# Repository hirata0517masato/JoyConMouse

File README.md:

# JoyConMouse
ホームポジションを崩さずにマウス操作をしたかったので自作  

# 仕様（サンプルコード）
ジョイスティック：マウス操作  
右キー：左クリック  
中央キー：右クリック  
左キー＋ジョイスティック：スクロール  
左キー＋中央キー：進む  
左キー＋右キー：戻る  
中央キー＋ジョイスティック：マウス操作（速度UP）

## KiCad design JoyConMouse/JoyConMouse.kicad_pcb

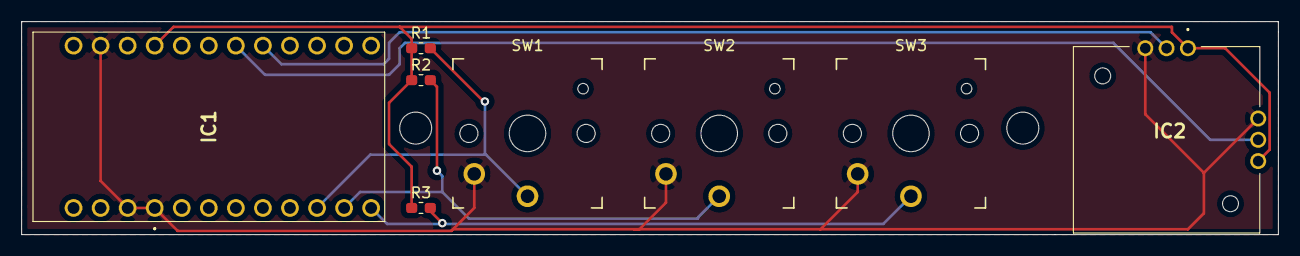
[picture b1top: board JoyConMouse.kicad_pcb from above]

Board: 2 copper layers, 118.0 x 20.0 mm, 8 parts (0 on the bottom side), 7 nets.

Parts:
IC1: DEV-12640; DEV12640
IC2: JT8P-3.2T-B10K-1-16Y; JT8P32TB10K116Y
R1, R2, R3: R; C_0603_1608Metric_Pad1.05x0.95mm_HandSolder
SW1, SW2, SW3: SW_Push; SW_PG1350

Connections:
+5V: IC1.18, IC2.A1, IC2.B1, R1.1, R2.1, R3.1
A0: IC1.A1, IC2.A2
A1: IC1.A2, IC2.B2
D7: IC1.7, R1.2, SW1.1
D8: IC1.8, R2.2, SW2.1
D9: IC1.9, R3.2, SW3.1
GND: IC1.1, IC1.20, IC1.24, IC2.A3, IC2.B3, SW1.2, SW2.2, SW3.2

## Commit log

2022-09-18 KiCad_date
    基板データの初回コミット
2022-09-25 first edition
    サンプルコードの作成および動作確認完了
2022-09-25 add_3D_body
    ケース用の３Dデータを追加
2022-09-25 Soft_Update
    コードの更新
    ・感度調整
    ・中央ボタンおしながらジョイスティック操作で通常時よりもはやくマウス操作ができる
2022-10-10 debug
    修正前：マウスの操作量が０の時も信号を送信する
    修正後：マウスの操作量が０の時は信号を送信しない
    補足：WakeOnLanを有効にしていると不要な信号によりなぜかPCが起動してしまう。
